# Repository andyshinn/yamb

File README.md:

# yamb

YAMB (Yet Another Meshtasic Board) is a meshtastic board centered around outdoor solar powered use. The goals of this project are:

* Learn more about PCB design and manufacturing.
* Build a Meshtastic board that has features I am always looking for in an outdoor solar node.
* Is open source and open hardware so anyone can make it, modify it, and use it.
* Get the board into hands of people near me that want to use it to help expand our local mesh network.

## Features

* Based around the proven RAK4630 module which provides the nrf52840 and SX1262 LoRa radio.
* Solar power and battery charging using the excellent Voltaic SVR and MCSBC combination.
* Reset supervisor to ensure the board can recover from power issues like brownouts.
* Vertical USB-C connector for easy access to the USB port while inside an enclosure.
* Ports for external power switch and reset button to aide maintenance while enclosed.
* Plenty of GPIO pins and ports for extending and hacking.
* Onboard QWIIC / STEMMA QT connector for easy I2C expansion.
* BME280 temperature, humidity, and pressure sensor.

## Schematic

## Notes

### Exporting Images

To export images from KiCad, you can use the following command in the terminal:

```bash
export KICAD9_3DMODEL_DIR=/Applications/KiCad/KiCad.app/Contents/SharedSupport/3dmodels
kicad-cli pcb export stl yamb.kicad_pcb --output exports/yamb-pcb.stl
kicad-cli pcb render --output=exports/yamb-pcb.png --rotate="310,0,45" --perspective --pan "0,2.2,0" --quality high --zoom 1.3 yamb.kicad_pcb
kicad-cli sch export svg yamb.kicad_sch -n --output exports
```

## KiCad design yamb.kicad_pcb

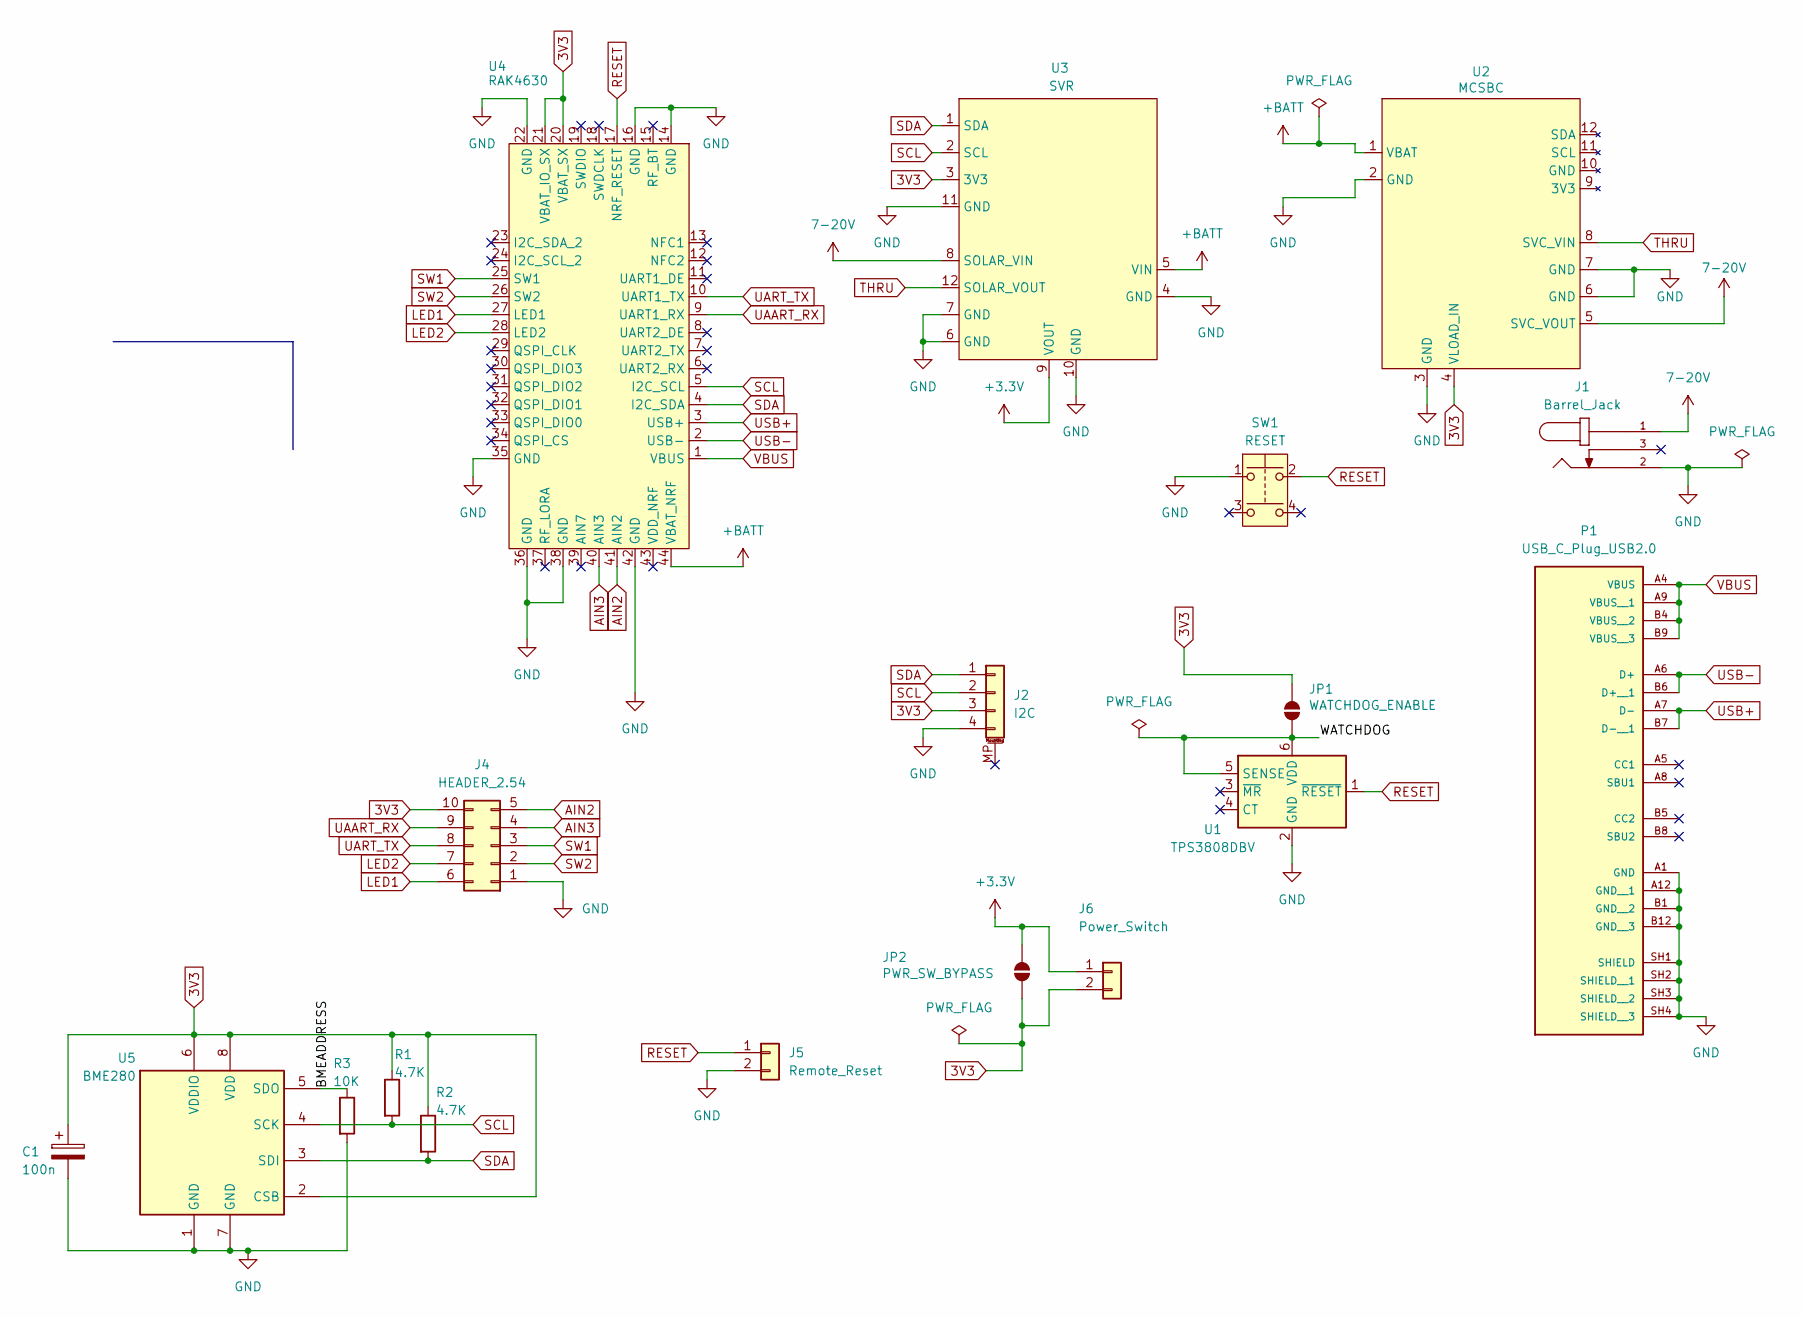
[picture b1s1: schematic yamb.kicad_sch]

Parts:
C1: 100n; C_1206_3216Metric_Pad1.33x1.80mm_HandSolder
J1: Barrel_Jack; CUI_PJ-044A; PARTREV 1.02
J2: I2C; JST_SH_BM04B-SRSS-TB_1x04-1MP_P1.00mm_Vertical
J4: HEADER_2.54; CONN_7024610xx_MOL
J5: Remote_Reset; CONN_SDA-70543-xxxx_02_MOL
J6: Power_Switch; CONN_SDA-70543-xxxx_02_MOL
JP1: WATCHDOG_ENABLE; SolderJumper-2_P1.3mm_Open_RoundedPad1.0x1.5mm
JP2: PWR_SW_BYPASS; SolderJumper-2_P1.3mm_Open_RoundedPad1.0x1.5mm
P1: USB_C_Plug_USB2.0; SAMESKY_UJ20-C-V-G-SMT-P16-TR; PARTREV 1.0
R1, R2: 4.7K; R_1206_3216Metric_Pad1.30x1.75mm_HandSolder
R3: 10K; R_1206_3216Metric_Pad1.30x1.75mm_HandSolder
SW1: RESET; SW_1825910-6-4
U1: TPS3808DBV; SOT-23-6
U2: MCSBC; Voltaic_MCSBC
U3: SVR; Voltaic_SVR
U4: RAK4630
U5: BME280; Bosch_LGA-8_2.5x2.5mm_P0.65mm_ClockwisePinNumbering

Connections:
3V3: C1.1, J2.3, J4.10, J6.2, JP1.1 (A), JP2.2 (B), R1.1, R2.1, U2.4 (VLOAD_IN), U3.3 (3V3), U4.20 (VBAT_SX), U4.21 (VBAT_IO_SX), U5.2 (CSB), U5.6 (VDDIO), U5.8 (VDD)
7-20V: J1.1, U2.5 (SVC_VOUT), U3.8 (SOLAR_VIN)
+3.3V: J6.1, JP2.1 (A), U3.9 (VOUT)
+BATT: U2.1 (VBAT), U3.5 (VIN), U4.44 (VBAT_NRF)
/BMEADDRESS: R3.1, U5.5 (SDO)
/WATCHDOG: JP1.2 (B), U1.5 (SENSE), U1.6 (VDD)
AIN2: J4.5, U4.41 (AIN2)
AIN3: J4.4, U4.40 (AIN3)
GND: C1.2, J1.2, J2.4, J4.1, J5.2, P1.A1 (GND), P1.A12 (GND__1), P1.B1 (GND__2), P1.B12 (GND__3), P1.SH1 (SHIELD), P1.SH2 (SHIELD__1), P1.SH3 (SHIELD__2), P1.SH4 (SHIELD__3), R3.2, SW1.1, U1.2 (GND), U2.2 (GND), U2.3 (GND), U2.6 (GND), U2.7 (GND), U3.4 (GND), U3.6 (GND), U3.7 (GND), U3.10 (GND), U3.11 (GND), U4.14 (GND), U4.16 (GND), U4.22 (GND), U4.35 (GND), U4.36 (GND), U4.38 (GND), U4.42 (GND), U5.1 (GND), U5.7 (GND)
LED1: J4.6, U4.27 (LED1)
LED2: J4.7, U4.28 (LED2)
RESET: J5.1, SW1.2, U1.1 (~RESET), U4.17 (NRF_RESET)
SCL: J2.2, R1.2, U3.2 (SCL), U4.5 (I2C_SCL), U5.4 (SCK)
SDA: J2.1, R2.2, U3.1 (SDA), U4.4 (I2C_SDA), U5.3 (SDI)
SW1: J4.3, U4.25 (SW1)
SW2: J4.2, U4.26 (SW2)
THRU: U2.8 (SVC_VIN), U3.12 (SOLAR_VOUT)
UAART_RX: J4.9, U4.9 (UART1_RX)
UART_TX: J4.8, U4.10 (UART1_TX)
USB+: P1.A7 (D-), P1.B7 (D-__1), U4.3 (USB+)
USB-: P1.A6 (D+), P1.B6 (D+__1), U4.2 (USB-)
VBUS: P1.A4 (VBUS), P1.A9 (VBUS__1), P1.B4 (VBUS__2), P1.B9 (VBUS__3), U4.1 (VBUS)

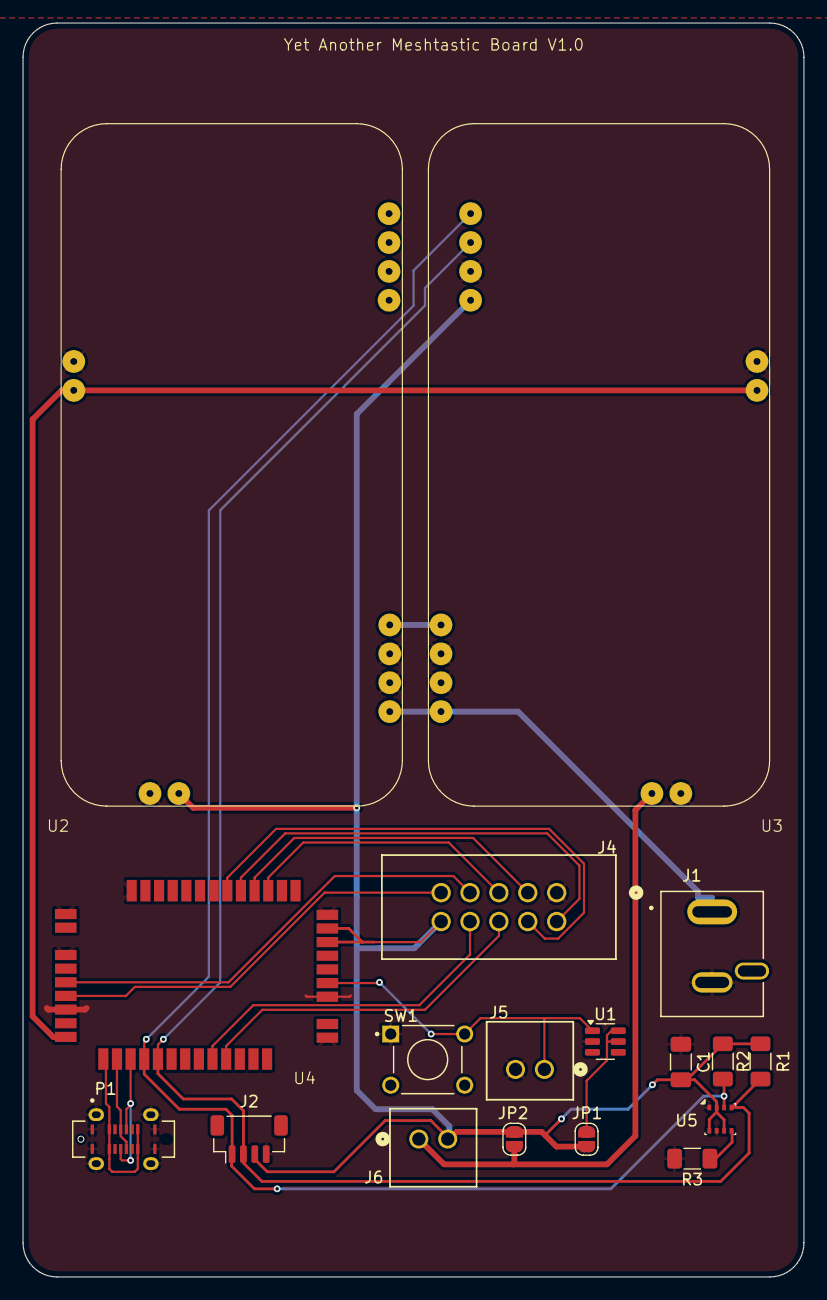
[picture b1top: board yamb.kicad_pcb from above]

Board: 2 copper layers, 68.7 x 110.2 mm, 18 parts (0 on the bottom side), 22 nets.

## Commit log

2025-06-05 yet another meshtastic board!
2025-06-06 still lots of errors
2025-06-23 voltaic footprints, adding to schematic
2025-06-24 additional footprints for reset, power switch, correct USB-C symbol for footprint, bypass jumpers for watchdog and pwr switch
2025-06-26 custom libraries
2025-06-27 solving ERC errors
2025-06-27 PCB layout first pass
2025-06-27 some board layout stuff
2025-06-29 some 3D components, adding BME280, some 3V3 vs 3.3V fixes
2025-06-29 see if kicanvas works without embedded file
2025-06-29 remove embedded rake4630 layout as well
2025-06-29 readme, image exports
2025-06-29 images are master
2025-06-29 schematic instead of model since that doesn't work in readme
2025-07-02 changed connectors to shroued 0.1" and cleaned some board DRC errors
2025-07-02 readme updates
2025-07-03 embed SVR photos
2025-07-03 embed photos of board
